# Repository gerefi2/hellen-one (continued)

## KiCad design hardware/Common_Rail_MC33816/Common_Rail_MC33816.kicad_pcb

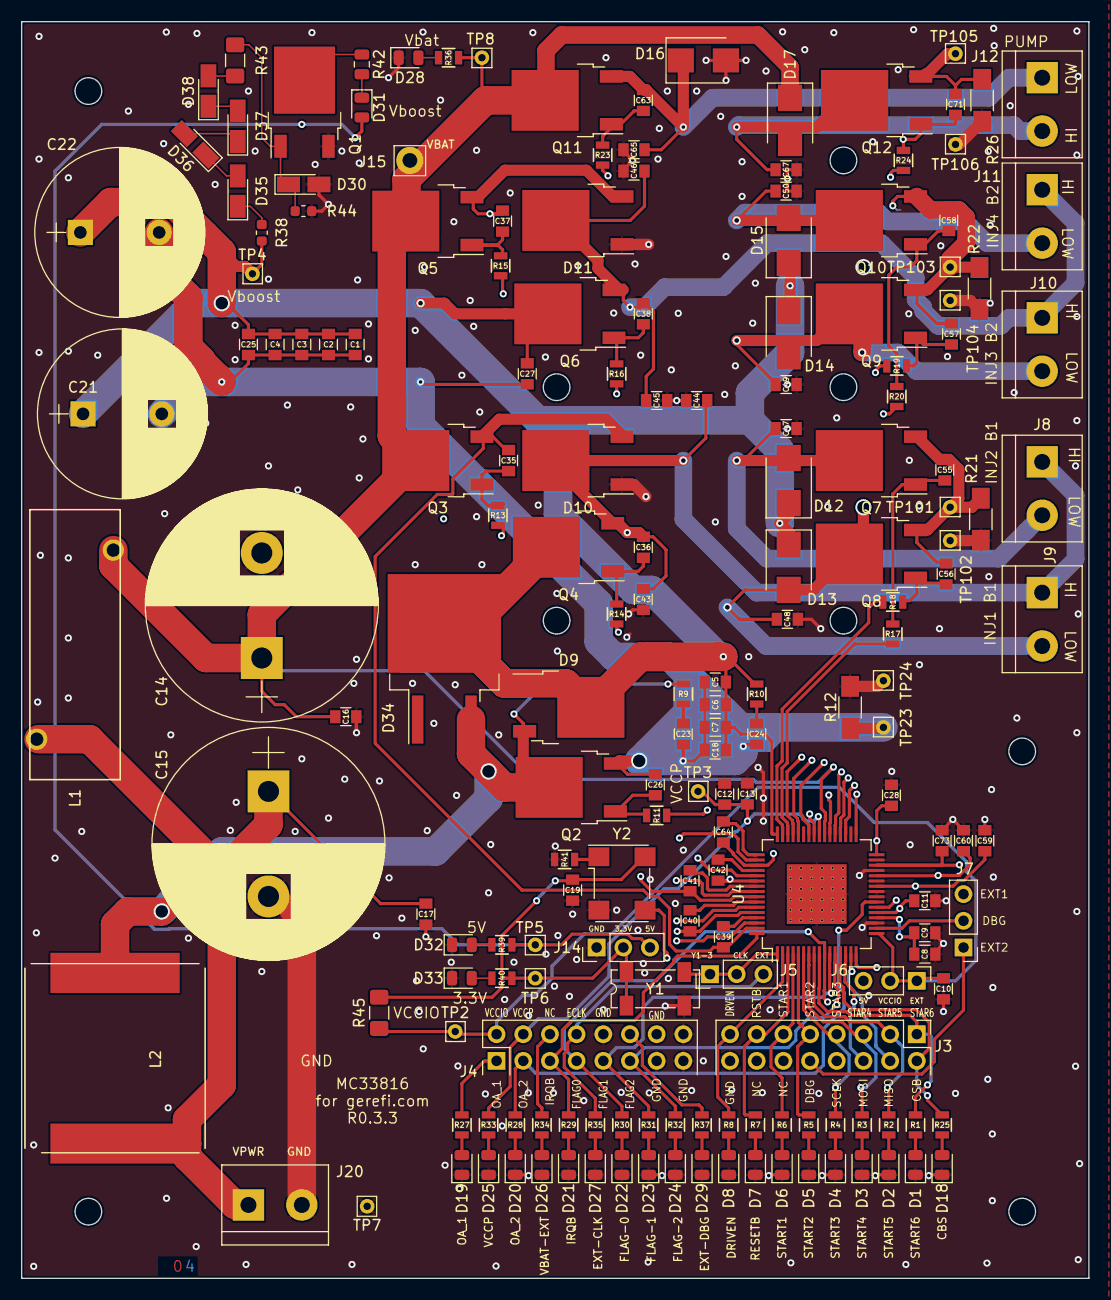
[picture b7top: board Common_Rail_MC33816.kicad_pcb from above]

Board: 4 copper layers, 101.6 x 119.6 mm, 183 parts (0 on the bottom side), 108 nets.

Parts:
C1, C3, C5, C7: 100nF; C_0805
C2, C4, C6, C18: 10nF; C_0805
C8, C10, C11, C13: 0.1uF; C_0805
C9: 1uF; C_0805
C12: 4.7uF; C_0805
C14, C15: 1000uF; CP_Radial_D22.0mm_P10.00mm_SnapIn
C16, C17: 220nF; C_0805
C19, C35, C36, C37, C38, C55, C56, C57, C58, C63, C71: 1000pF; C_0805
C21, C22: 390uF; CP_Radial_D16.0mm_P7.50mm
C23, C24, C28, C59, C60, C73: 330pF; C_0805
C25, C27: 0.22uF; C_0805
C26: 470pF; C_0805
C39, C40, C41, C42, C64: 0.33uF; C_0805
C43, C44, C45, C46, C47, C48, C49, C50, C65, C67: 4700pF; C_0805
D1, D2, D3, D4, D5, D6, D7, D8, D18, D19, D20, D21, D22, D23, D24, D25, D26, D27, D28, D29, D31, D32, D33: LED_Small; LED_0805_2012Metric
D9: FFD10UP20S; TO-252-2
D10, D11: SBR10200CTL; TO-252-2
D12, D13, D14, D15, D16, D17: STPS2H100UY; D_SMB
D30, D35, D36, D37, D38: 5.7V; D_MicroMELF_Handsoldering
D34: STTH802G-TR; TO-263-2
J3, J4: CONN_02X08; Pin_Header_Straight_2x08_Pitch2.54mm
J5, J6, J7, J14: CONN_01X03; Pin_Header_Straight_1x03_Pitch2.54mm
J8, J9, J10, J11, J12: INJ_Term; TerminalBlock_bornier-2_P5.08mm
J15: CONN_01X01; Pin_D1.4mm_L8.5mm_W2.8mm_FlatFork
J20: Conn_01x02; TerminalBlock_bornier-2_P5.08mm
L1: 6uH; 744710610-Inductor
L2: 10uH; IHLP6767GZER100M01
Q1, Q2, Q3, Q4, Q5, Q6, Q7, Q8, Q9, Q10, Q11, Q12: BUK9230-100B; TO-252-2
R1, R2, R3, R4, R5, R6, R7, R8, R25, R27, R28, R29, R30, R31, R32, R33, R34, R35, R36, R37, R39, R40: 1k; R_0805
R9, R10: 5.1R; R_0805
R11, R13, R14, R15, R16, R17, R18, R19, R20, R23, R24, R41: 10R; R_0805
R12, R21, R22, R26: 0R010; R_1206_HandSoldering
R38, R44: 10k; R_0603_1608Metric
R42: 1k; R_0805_2012Metric
R43, R45: 0R010; R_1206_3216Metric_Pad1.42x1.75mm_HandSolder
TP2, TP3, TP4, TP5, TP6, TP7, TP8, TP23, TP24, TP101, TP102, TP103, TP104, TP105, TP106: CONN_01X01; Pin_D0.7mm_L6.5mm_W1.8mm_FlatFork
U4: MC33816; HTQFP-64-1EP_10x10mm_Pitch0.5mm_ThermalPad_for_MC33816
Y1: 1MHz; Crystal_SMD_SeikoEpson_MC306-4pin_8.0x3.2mm
Y2: 1MHz; Oscillator_SMD_Diodes_FN-4Pin_7.0x5.0mm

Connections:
/3.3V: C19.1, J14.2, R40.2, R45.1, TP6.1, Y1.1, Y1.4, Y2.4
/5V: C11.1, D31.2, J6.3, J14.3, R39.2, TP5.1, U4.21
/BANK1_BAT: C35.2, C39.2, D10.3, Q3.3, U4.63
/BANK2_BAT: C37.2, C41.2, D11.3, Q5.3, U4.57
/CLK: J5.1, J5.2, U4.1, Y1.3, Y2.3
/CSB: J3.2, R25.2, U4.13
/DBG: J7.2, U4.18
/DBG_EXT1: J4.12, J7.3, R37.2
/DBG_EXT2: J3.10, J7.1
/DRVEN: J3.15, R8.2, U4.2
/EXT_CLK: J4.8, J5.3, R35.2
/FLAG_0: J4.7, R30.2, U4.10
/FLAG_1: J4.9, R31.2, U4.11
/FLAG_2: J4.11, R32.2, U4.12
/G_HB1_BAT: R13.2, U4.62
/G_HB1_BST: R14.2, U4.59
/G_HB2_BAT: R15.2, U4.56
/G_HB2_BST: R16.2, U4.53
/G_LS6: R23.2, U4.50
/G_L_BOOST: R11.2, U4.41
/G_L_INJ1: R18.2, U4.47
/G_L_INJ2: R17.2, U4.46
/G_L_INJ3: R19.2, U4.45
/G_L_INJ4: R20.2, U4.44
/G_PUMP: R24.2, U4.42
/INJ1_LOW: C48.1, D13.2, J9.2, Q8.2, U4.38
/INJ2_LOW: C47.1, D12.2, J8.2, Q7.2, U4.37
/INJ3_LOW: C49.1, D14.2, J10.2, Q9.2, U4.36
/INJ4_LOW: C50.1, D15.2, J11.2, Q10.2, U4.35
/INJ_B1_HIGH: C36.2, C40.2, C43.1, C44.1, D10.2, J8.1, J9.1, Q4.3, U4.60
/INJ_B2_HIGH: C38.2, C42.2, C45.1, C46.1, D11.2, J10.1, J11.1, Q6.3, U4.54
/IRQB: J4.5, R29.2, U4.64
/MISO: J3.4, U4.15
/MOSI: J3.6, U4.14
/OA_1: J4.1, R27.2, U4.22
/OA_2: J4.3, R28.2, U4.23
/PUMP_HIGH: C63.2, C64.1, C65.1, D16.1, J12.1, Q11.3, U4.51
/PUMP_LOW: C67.1, D17.2, J12.2, Q12.2, U4.33
/P_B1_SENSE: C55.1, C56.1, C59.1, Q7.3, Q8.3, R21.1, TP101.1, U4.26
/P_B2_SENSE: C57.1, C58.1, C60.1, Q9.3, Q10.3, R22.1, TP103.1, U4.28
/P_SENSE_BOOST: C1.2, C2.2, C3.2, C4.2, C5.2, C6.2, C7.2, C18.2, C21.2, C22.2, C23.2, C24.2, C25.2, C26.1, C27.2, C28.1, Q2.3, R12.1, TP23.1, U4.32
/P_SENSE_PUMP: C71.1, C73.1, Q12.3, R26.1, TP105.1, U4.30
/RESETB: J3.13, R7.2, U4.3
/SCLK: J3.8, U4.16
/START1: J3.11, R6.2, U4.4
/START2: J3.9, R5.2, U4.5
/START3: J3.7, R4.2, U4.6
/START4: J3.5, R3.2, U4.7
/START5: J3.3, R2.2, U4.8
/START6: J3.1, R1.2, U4.9
/VBAT_EXT: J4.6, R34.2
/VCC2P5: C8.1, C9.1, U4.20
/VCCIO: C10.1, J4.2, J6.1, J6.2, R45.2, TP2.1, U4.17
/VCCP: C12.1, C13.1, J4.4, R33.2, TP3.1, U4.40
/Vbat: C14.1, C16.1, D17.1, J15.1, L1.2, Q3.2, Q5.2, Q11.2, R36.2, TP8.1, U4.39
/Vboost: C1.1, C2.1, C3.1, C4.1, C5.1, C6.1, C7.1, C18.1, C21.1, C22.1, C25.1, C27.1, D9.1, D9.2, D12.1, D13.1, D14.1, D15.1, D34.2, Q4.2, Q6.2, R10.1, R38.2, TP4.1, U4.48
/Vbuck: D9.3, D34.3, L2.1, Q2.2, R9.1
/Vpwr: C15.1, C17.1, J20.1, L1.1, L2.2
GND: C8.2, C9.2, C10.2, C11.2, C12.2, C13.2, C14.2, C15.2, C16.2, C17.2, C19.2, C28.2, C43.2, C44.2, C45.2, C46.2, C47.2, C48.2, C49.2, C50.2, C59.2, C60.2, C65.2, C67.2, C73.2, D1.1, D2.1, D3.1, D4.1, D5.1, D6.1, D7.1, D8.1, D10.1, D11.1, D16.2, D18.1, D19.1, D20.1, D21.1, D22.1, D23.1, D24.1, D25.1, D26.1, D27.1, D28.1, D29.1, D30.2, D32.1, D33.1, J3.16, J4.10, J4.13, J4.15, J4.16, J14.1, J20.2, Q1.3, R12.2, R21.2, R22.2, R26.2, R41.1, R44.1, TP7.1, TP24.1, TP102.1, TP104.1, TP106.1, U4.19, U4.24, U4.25, U4.27, U4.29, U4.31, U4.65, Y1.2, Y2.2
unnamed: C23.1, R9.2
unnamed: C24.1, R10.2
unnamed: C26.2, Q2.1, R11.1
unnamed: C35.1, Q3.1, R13.1
unnamed: C36.1, Q4.1, R14.1
unnamed: C37.1, Q5.1, R15.1
unnamed: C38.1, Q6.1, R16.1
unnamed: C39.1, U4.61
unnamed: C40.1, U4.58
unnamed: C41.1, U4.55
unnamed: C42.1, U4.52
unnamed: C55.2, Q7.1, R17.1
unnamed: C56.2, Q8.1, R18.1
unnamed: C57.2, Q9.1, R19.1
unnamed: C58.2, Q10.1, R20.1
unnamed: C63.1, Q11.1, R23.1
unnamed: C64.2, U4.49
unnamed: C71.2, Q12.1, R24.1
unnamed: D1.2, R1.1
unnamed: D2.2, R2.1
unnamed: D3.2, R3.1
unnamed: D4.2, R4.1
unnamed: D5.2, R5.1
unnamed: D6.2, R6.1
unnamed: D7.2, R7.1
unnamed: D8.2, R8.1
unnamed: D18.2, R25.1
unnamed: D19.2, R27.1
unnamed: D20.2, R28.1
unnamed: D21.2, R29.1
unnamed: D22.2, R30.1
unnamed: D23.2, R31.1
unnamed: D24.2, R32.1
unnamed: D25.2, R33.1
unnamed: D26.2, R34.1
unnamed: D27.2, R35.1
unnamed: D28.2, R36.1
unnamed: D29.2, R37.1
unnamed: D30.1, Q1.1, R43.2, R44.2
unnamed: D31.1, R42.2
unnamed: D32.2, R39.1
unnamed: D33.2, R40.1
unnamed: D35.1, R38.1
unnamed: D35.2, D36.1
unnamed: D36.2, D37.1
unnamed: D37.2, D38.1
unnamed: D38.2, R43.1
unnamed: Q1.2, R42.1
unnamed: R41.2, Y2.1

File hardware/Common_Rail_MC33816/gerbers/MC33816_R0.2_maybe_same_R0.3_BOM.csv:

Reference, Quantity, Value, Footprint, Datasheet, MFG,MFG#, VEND1,VEND1#, VEND2,VEND2#
C10 C11 C13 C8 ,4,0.1uF,gerefi_LIB:C_0805,,AVX,08055C104MAT2A,DIGI,478-3351-1-ND,JLCPCB,C49678
C12 ,1,4.7uF,gerefi_LIB:C_0805,,Taiyo Yuden,TMK212AB7475KG-T,DIGI,587-2990-1-ND,JLCPCB,C1779
C14 C15 ,2,1000uF,Capacitors_ThroughHole:CP_Radial_D22.0mm_P10.00mm_SnapIn,,Cornell,SLPX102M100A3P3,DIGI,338-1553-ND,,
C21 C22 ,2,390uF,Capacitors_ThroughHole:CP_Radial_D16.0mm_P7.50mm,,Nichicon,UHE2A391MHD,DIGI,493-1680-ND,,
C16 C17 C25 C27 ,4,0.22uF,gerefi_LIB:C_0805,,KEMET,C0805C224M1RACTU,DIGI,399-9205-1-ND,,
C26 ,1,470pF,gerefi_LIB:C_0805,,TDK,CGA4C2C0G2A471J060AA,DIGI,445-6953-1-ND,JLCPCB,C1743
C35 C36 C37 C38 C55 C56 C57 C58 C63 C71 ,10,1000pF,gerefi_LIB:C_0805,,avx,08051C102KAT2A,DIGI,478-1352-1-ND,JLCPCB,C209838
C39 C40 C41 C42 C64 ,5,0.33uF,gerefi_LIB:C_0805,,Yageo,CC0805KKX7R8BB334,DIGI,311-3385-1-ND,JLCPCB,C1740
C43 C44 C45 C46 C47 C48 C49 C50 C65 C67 ,10,4700pF,gerefi_LIB:C_0805,,TDK,C2012C0G2A472J125AA,DIGI,445-2324-1-ND,JLCPCB,C21217
C23 C24 C28 C59 C60 C73 ,6,330pF,gerefi_LIB:C_0805,,Kemet,C0805C331J1GACTU,DIGI,399-1131-1-ND,JLCPCB,C51207
C9 ,1,1uF,gerefi_LIB:C_0805,,Yageo,CC0805KKX7R8BB105,DIGI,311-1456-1-ND,JLCPCB,C28323
D10 D11 ,2,SBR10200CTL,TO_SOT_Packages_SMD:TO-252-2Lead,,Diodes,SBR10200CTL-13,DIGI,SBR10200CTL-13DICT-ND,,
D12 D13 D14 D15 D16 D17 ,6,STPS2H100UY,Diodes_SMD:D_SMB,,ST,STPS2H100UY,DIGI,497-11093-1-ND,,
D9 ,1,FFD10UP20S,TO_SOT_Packages_SMD:TO-252-2Lead,,ONSEMI,FFD10UP20S,DIGI,FFD10UP20SCT-ND,,
J10 J11 J12 J8 J9 ,5,INJ_Term,Terminal_Blocks:TerminalBlock_bornier-2_P5.08mm,,onshore,OSTTG025100B,DIGI,ED2703-ND,,
J15 ,1,CONN_01X01,Pin_Headers:Pin_Header_Straight_1x01_Pitch2.54mm,
J20 ,1,Conn_01x02,Connect:PINHEAD1-2,,TE,282834-2,DIGI,A98333-ND,
J3 J4 ,2,CONN_02X08,Pin_Headers:Pin_Header_Straight_2x08_Pitch2.54mm,,sullins,SBH11-PBPC-D08-ST-BK,DIGI,S9171-ND,,
J14 J5 J6 J7 ,4,CONN_01X03,Pin_Headers:Pin_Header_Straight_1x03_Pitch2.54mm,
L1 ,1,6uH,gerefi_LIB:744710610-Inductor,,Würth Elektronik,744710610,DIGI,732-3255-ND,,
L2 ,1,10uH,gerefi_LIB:IHLP6767GZER100M01,,Vishay,IHLP6767GZER100M01,DIGI,541-1259-1-ND,,
Q10 Q11 Q12 Q2 Q3 Q4 Q5 Q6 Q7 Q8 Q9 ,11,BUK9230-100B,TO_SOT_Packages_SMD:TO-252-2Lead,,Nexperia,BUK9230-100B,DIGI,1727-4708-1-ND,,
R12 ,1,0R010,Resistors_SMD:R_1206_HandSoldering,,Ohmite,MCS1632R010FER,DIGI,MCS1632R010FERCT-ND,,
R11 R13 R14 R15 R16 R17 R18 R19 R20 R23 R24 ,11,10R,gerefi_LIB:R_0805,,Stackpole,RMCF0805JG10R0,DIGI,RMCF0805JG10R0CT-ND,JLCPCB,C17403
R21 R22 R26 ,3,0R015,Resistors_SMD:R_1206_HandSoldering,,Panasonic,ERJ-8CWFR015V,DIGI,P0.015BVCT-ND,JLCPCB,C201281
R10 R9 ,2,5.1R,gerefi_LIB:R_0805,,Stackpole,RMCF0805JT5R10,DIGI,RMCF0805JT5R10CT-ND,JLCPCB,C247080
TP101 TP102 TP103 TP104 TP105 TP106 TP23 TP24 ,8,CONN_01X01,Connect:PINTST,
U4 ,1,MC33816,gerefi_LIB:HTQFP-64-1EP_10x10mm_Pitch0.5mm_ThermalPad_for_MC33816,,FreeScale,MC33816AE,Mouser,841-MC33816AE,,
Y1 ,1,1MHz,Crystals:Crystal_SMD_SeikoEpson_MC306-4pin_8.0x3.2mm,,epson,SG7050CAN 1.000000M-TJGA3,DIGI,SER3990CT-ND,

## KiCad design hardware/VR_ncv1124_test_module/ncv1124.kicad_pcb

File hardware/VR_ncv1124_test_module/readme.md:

Not suitable for crank sensor. Use this for your wheel speed or transmission shaft.

On stm32 consider using together with https://github.com/gerefi/gerefi-hardware/tree/main/frequency-divider

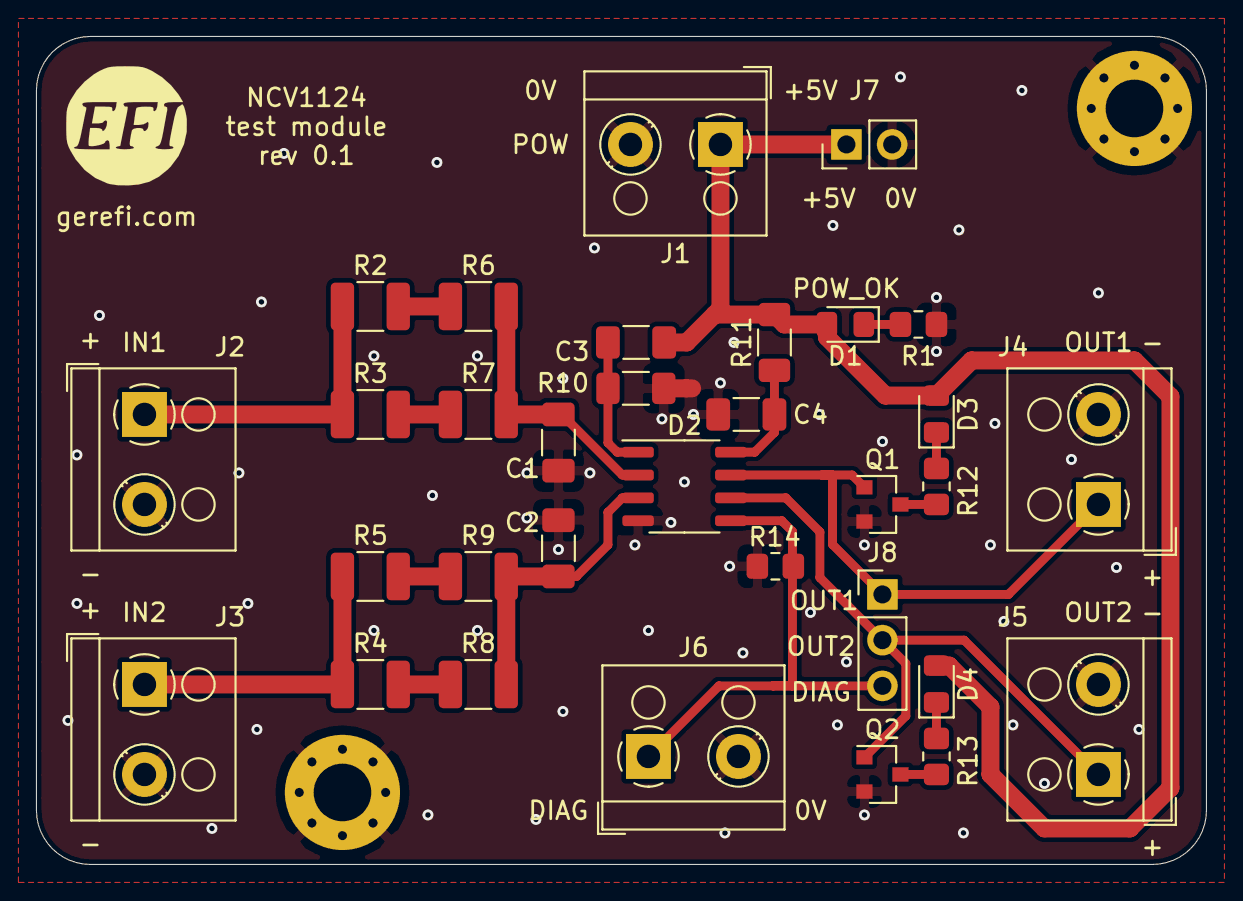
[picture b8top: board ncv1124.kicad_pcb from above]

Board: 2 copper layers, 65.0 x 46.0 mm, 35 parts (0 on the bottom side), 20 nets.

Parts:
C1, C2, C3: 0.022u; C_1206_3216Metric_Pad1.33x1.80mm_HandSolder
C4: 0.22u; C_1206_3216Metric_Pad1.33x1.80mm_HandSolder
D1, D3, D4: LED; LED_0805_2012Metric_Pad1.15x1.40mm_HandSolder
D2: NCV1124; SO-8_3.9x4.9mm_P1.27mm
G1: LOGO
H1, H2: MountingHole_Pad; MountingHole_3.2mm_M3_Pad_Via
J1, J2, J3, J4, J5, J6: Screw_Terminal_01x02; TerminalBlock_RND_205-00001_1x02_P5.00mm_Horizontal
J7: Conn_01x02_Male; PinHeader_1x02_P2.54mm_Vertical
J8: Conn_01x03_Male; PinHeader_1x03_P2.54mm_Vertical
Q1, Q2: 2N7002; SOT-23
R1, R12, R13, R14: 3K; R_0805_2012Metric_Pad1.20x1.40mm_HandSolder
R2, R3, R4, R5, R6, R7, R8, R9: 22k; R_1210_3225Metric_Pad1.30x2.65mm_HandSolder
R10: 24k; R_1206_3216Metric_Pad1.30x1.75mm_HandSolder
R11: 39; R_1206_3216Metric_Pad1.30x1.75mm_HandSolder

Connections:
+5V: C3.1, D1.2, D3.2, D4.2, J1.1, J7.1, R11.2
GND: C1.2, C2.2, C4.2, D2.4, H1.1, H2.1, J1.2, J2.2, J3.2, J4.2, J5.2, J6.2, J7.2, Q1.2, Q2.2, R1.1, R10.1, R14.1
unnamed: C1.1, D2.2, R6.2, R7.2
unnamed: C2.1, D2.3, R8.2, R9.2
unnamed: C3.2, D2.1, R10.2
unnamed: C4.1, D2.8, R11.1
unnamed: D1.1, R1.2
unnamed: D2.5, J6.1, J8.3, R14.2
unnamed: D2.6, J5.1, J8.2, Q2.1
unnamed: D2.7, J4.1, J8.1, Q1.1
unnamed: D3.1, R12.2
unnamed: D4.1, R13.2
unnamed: J2.1, R2.1, R3.1
unnamed: J3.1, R4.1, R5.1
unnamed: Q1.3, R12.1
unnamed: Q2.3, R13.1
unnamed: R2.2, R6.1
unnamed: R3.2, R7.1
unnamed: R4.2, R8.1
unnamed: R5.2, R9.1
